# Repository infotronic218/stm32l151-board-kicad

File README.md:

# STM32L151 board design with KiCad 
The design files are available and free to use . The Bill of materials is in Excel format and be ordered from Mouser website. For Any project related question do not hesitate to message me thanks.
## Manufactured board view

## Board Layout 3D View 

## Board Layout View 2

## Board Layout View 2

# List of sensors used in the design 
* Accelorometer 
* Analog Temperature sensor
* Digital Humidity and temperature sensor (I2C)
* External Flash memory (16Mbits)
* Digital RGB LED (IN-PI554FCH)
* Simple LED

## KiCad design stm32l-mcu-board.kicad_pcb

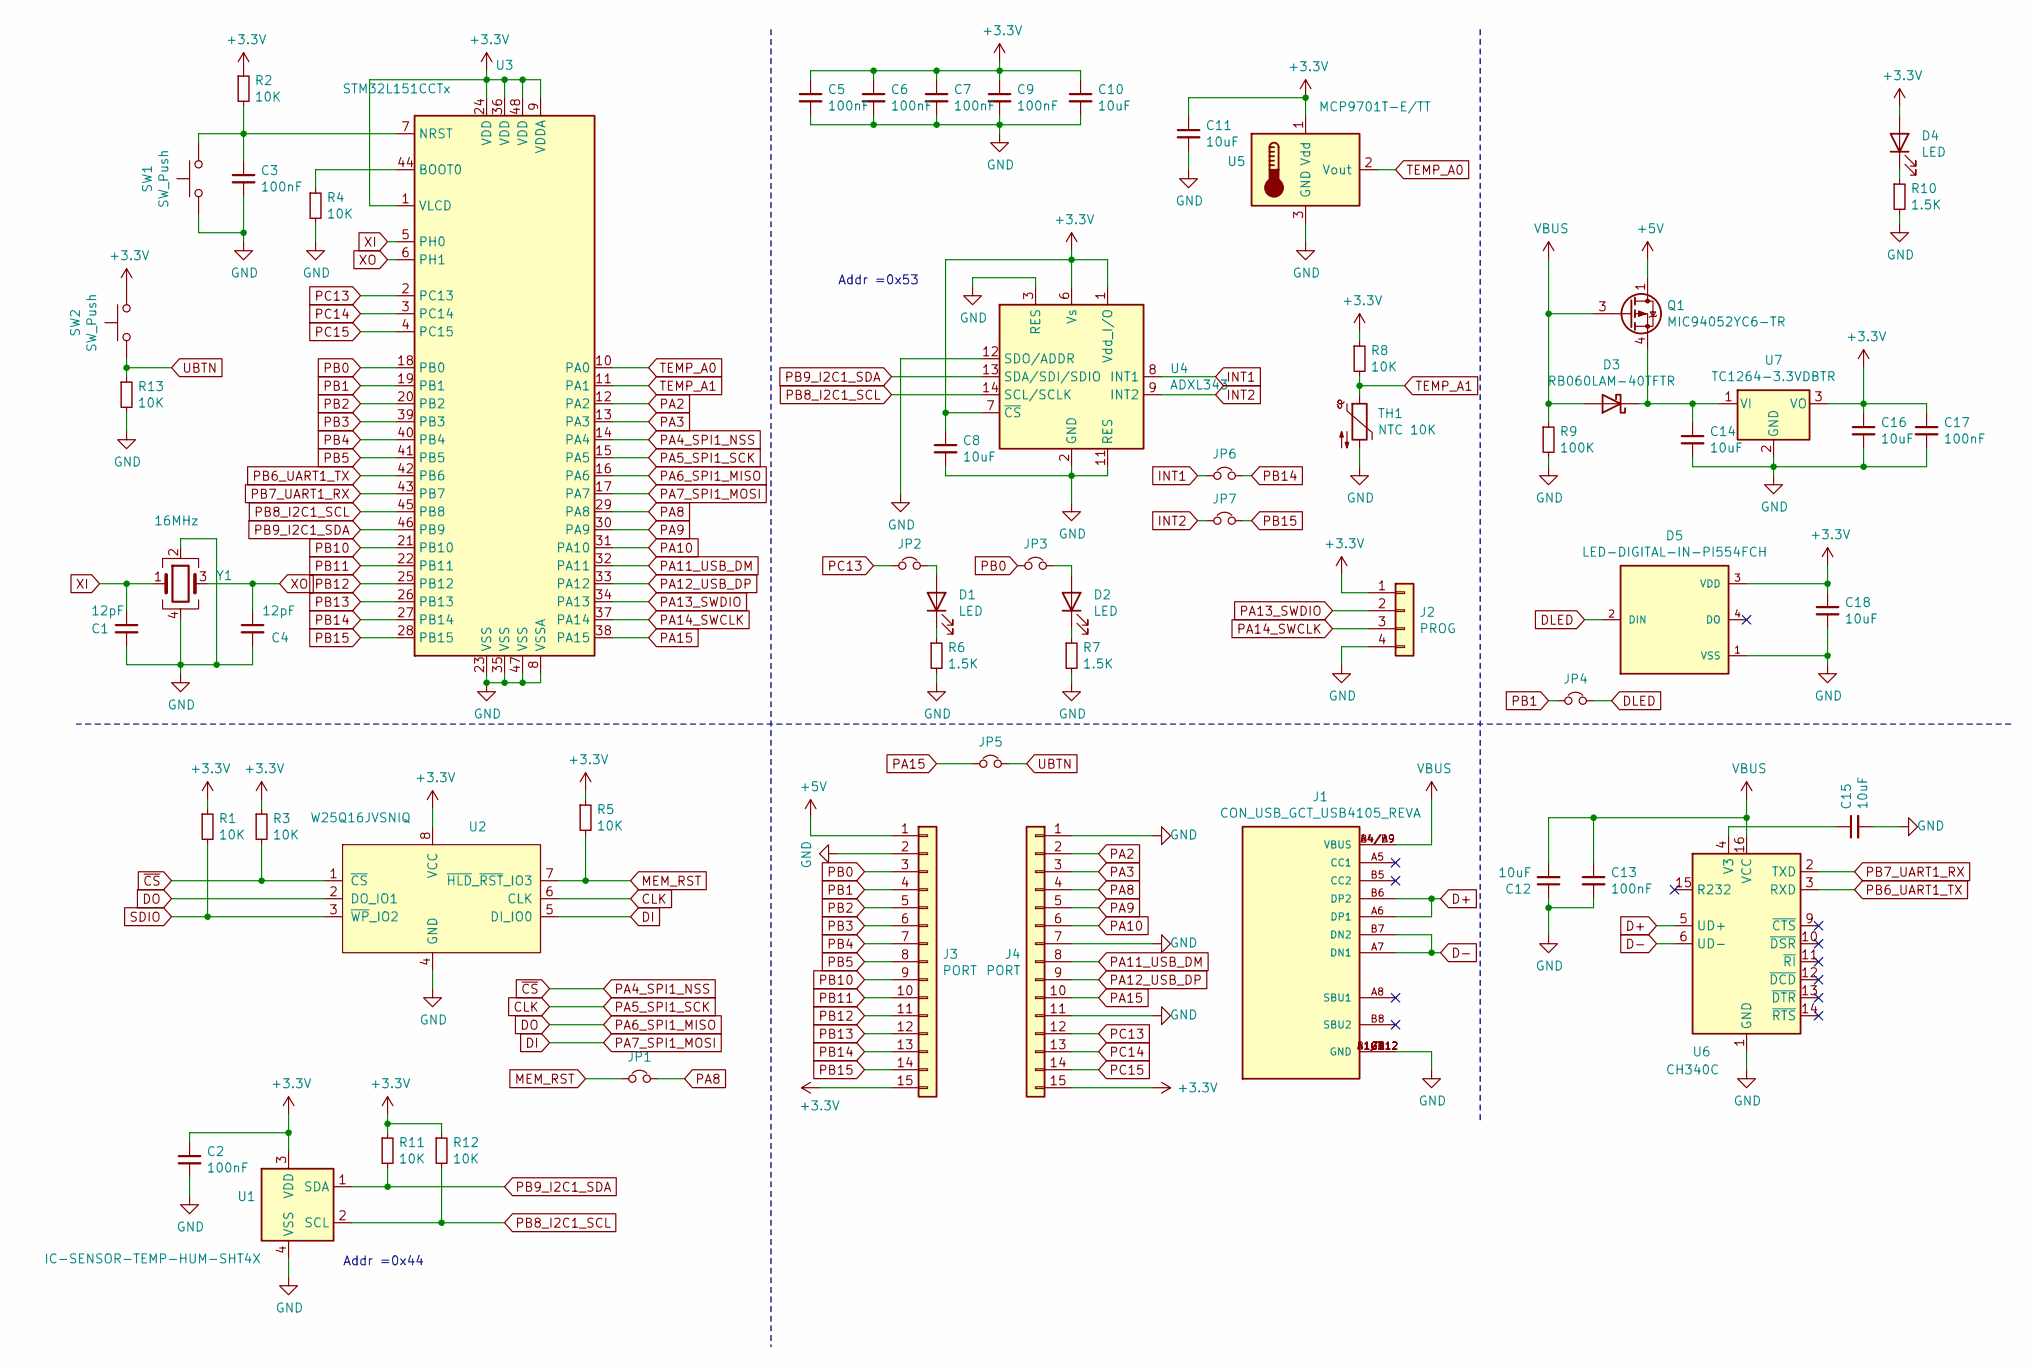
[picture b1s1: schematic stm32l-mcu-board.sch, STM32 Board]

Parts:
C1, C4: 12pF; C_0603_1608Metric; MPN 06035A120JAT2A; Mouser 581-06035A120J
C2, C3, C5, C6, C7, C9, C13, C17: 100nF; C_0603_1608Metric; MPN C0603C104K4RACTU; Mouser 80-C0603C104K4R
C8, C10, C11, C12, C14, C15, C16, C18: 10uF; C_0805_2012Metric; MPN C0805C106K3PACTU; Mouser 80-C0805C106K3P
D1, D2, D4: LED; LED_0805_2012Metric; MPN AP2012HD; Mouser 604-AP2012HD
D3: RB060LAM-40TFTR; D_SOD-128; MPN RB060LAM-40TFTR; Mouser 755-RB060LAM-40TFTR
D5: LED-DIGITAL-IN-PI554FCH; MPN IN-PI554FCH; Mouser 743-IN-PI554FCH
J1: CON_USB_GCT_USB4105_REVA; PARTREV 0.2; Mouser 640-USB4105-GF-A-060
J2: PROG; PinHeader_1x04_P2.54mm_Vertical
J3, J4: PORT; PinHeader_1x15_P2.54mm_Vertical
JP1, JP2, JP3, JP4, JP5, JP6, JP7: Jumper_NC_Small; SolderJumper-2_P1.3mm_Open_RoundedPad1.0x1.5mm
Q1: MIC94052YC6-TR; SOT-363_SC-70-6; MPN MIC94052YC6-TR; Mouser 998-MIC94052YC6TR
R1, R2, R3, R4, R5, R8, R11, R12, R13: 10K; R_0805_2012Metric; MPN CR0805-FX-1002ELF; Mouser 652-CR0805FX-1002ELF
R6, R7, R10: 1.5K; R_0805_2012Metric; MPN RCC08051K50FKEA; Mouser 71-RCC08051K50FKEA
R9: 100K; R_0805_2012Metric; MPN CHP0805AFX-1003ELF; Mouser 652-CHP0805AFX1003EL
SW1, SW2: SW_Push; SW_SPST_B3U-1000P-B
TH1: NTC 10K; R_0805_2012Metric; MPN ABNTC-0805-103J-3950F-T; Mouser 815-NTC805103J3950FT
U1: IC-SENSOR-TEMP-HUM-SHT4X; MPN SHT40-AD1B-R3; Mouser 403-SHT40-AD1B-R3
U2: W25Q16JVSNIQ; IC-FLASH-16MB-W25Q16JVSNIQ; MPN W25Q16JVSNIQ; Mouser 454-W25Q16JVSNIQ
U3: STM32L151CCTx; LQFP-48_7x7mm_P0.5mm; MPN STM32L151CCT6; Mouser 511-STM32L151CCT6
U4: ADXL343; LGA-14_3x5mm_P0.8mm_LayoutBorder1x6y; MPN ADXL343BCCZ-RL7; Mouser 584-ADXL343BCCZ-R7
U5: MCP9701T-E/TT; SOT-23; MPN MCP9701T-E/TT; Mouser 579-MCP9701T-E/TT
U6: CH340C; SOIC-16_3.9x9.9mm_P1.27mm
U7: TC1264-3.3VDBTR; SOT-223-3_TabPin2; MPN TC1264-3.3VDBTR; Mouser 579-TC1264-3.3VDBTR
Y1: 16MHz; Crystal_SMD_3225-4Pin_3.2x2.5mm; MPN CX3225SB16000E0EGFCC; Mouser 581-CX3225SB16000EGF

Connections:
+3V3: C2.1, C5.1, C6.1, C7.1, C8.1, C9.1, C10.1, C11.1, C16.1, C17.1, C18.1, D4.2 (A), D5.3 (VDD), J2.1, J3.15, J4.15, R1.1, R2.1, R3.1, R5.1, R8.1, R11.1, R12.1, SW2.2, U1.3 (VDD), U2.8 (VCC), U3.1 (VLCD), U3.9 (VDDA), U3.24 (VDD), U3.36 (VDD), U3.48 (VDD), U4.1 (Vdd_I/O), U4.6 (Vs), U4.7 (~CS), U5.1 (Vdd), U7.3 (VO)
+5V: J3.1, Q1.1 (D), Q1.2 (S), Q1.5 (D), Q1.6 (D)
CLK: U2.6 (CLK), U3.15 (PA5)
D+: J1.A6 (DP1), J1.B6 (DP2), U6.5 (UD+)
D-: J1.A7 (DN1), J1.B7 (DN2), U6.6 (UD-)
DI: U2.5 (DI_IO0), U3.17 (PA7)
DLED: D5.2 (DIN), JP4.2
DO: U2.2 (DO_IO1), U3.16 (PA6)
GND: C1.2, C2.2, C3.2, C4.2, C5.2, C6.2, C7.2, C8.2, C9.2, C10.2, C11.2, C12.1, C13.2, C14.2, C15.2, C16.2, C17.2, C18.2, D5.1 (VSS), J1.A1/B12 (GND), J1.B1/A12 (GND), J1.G1 (GND), J1.G2 (GND), J1.G3 (GND), J1.G4 (GND), J2.4, J3.2, J4.1, J4.7, J4.11, R4.2, R6.2, R7.2, R9.2, R10.2, R13.2, SW1.1, TH1.2, U1.4 (VSS), U2.4 (GND), U3.8 (VSSA), U3.23 (VSS), U3.35 (VSS), U3.47 (VSS), U4.2 (GND), U4.3 (RES), U4.4 (GND), U4.5 (GND), U4.11 (RES), U4.12 (SDO/ADDR), U5.3 (GND), U6.1 (GND), U7.2 (GND), Y1.2, Y1.4
INT1: JP6.1, U4.8 (INT1)
INT2: JP7.1, U4.9 (INT2)
MEM_RST: JP1.1, R5.2, U2.7 (~HLD~_~RST~_IO3)
unnamed: C3.1, R2.2, SW1.2, U3.7 (NRST)
unnamed: C14.1, D3.1 (K), Q1.4 (S), U7.1 (VI)
unnamed: C15.1, U6.4 (V3)
unnamed: D1.1 (K), R6.1
unnamed: D1.2 (A), JP2.2
unnamed: D2.1 (K), R7.1
unnamed: D2.2 (A), JP3.2
unnamed: D4.1 (K), R10.1
unnamed: R4.1, U3.44 (BOOT0)
PA2: J4.2, U3.12 (PA2)
PA3: J4.3, U3.13 (PA3)
PA4_SPI1_NSS: R3.2, U2.1 (~CS), U3.14 (PA4)
PA8: J4.4, JP1.2, U3.29 (PA8)
PA9: J4.5, U3.30 (PA9)
PA10: J4.6, U3.31 (PA10)
PA11_USB_DM: J4.8, U3.32 (PA11)
PA12_USB_DP: J4.9, U3.33 (PA12)
PA13_SWDIO: J2.2, U3.34 (PA13)
PA14_SWCLK: J2.3, U3.37 (PA14)
PA15: J4.10, JP5.1, U3.38 (PA15)
PB0: J3.3, JP3.1, U3.18 (PB0)
PB1: J3.4, JP4.1, U3.19 (PB1)
PB2: J3.5, U3.20 (PB2)
PB3: J3.6, U3.39 (PB3)
PB4: J3.7, U3.40 (PB4)
PB5: J3.8, U3.41 (PB5)
PB6_UART1_TX: U3.42 (PB6), U6.3 (RXD)
PB7_UART1_RX: U3.43 (PB7), U6.2 (TXD)
PB8_I2C1_SCL: R12.2, U1.2 (SCL), U3.45 (PB8), U4.14 (SCL/SCLK)
PB9_I2C1_SDA: R11.2, U1.1 (SDA), U3.46 (PB9), U4.13 (SDA/SDI/SDIO)
PB10: J3.9, U3.21 (PB10)
PB11: J3.10, U3.22 (PB11)
PB12: J3.11, U3.25 (PB12)
PB13: J3.12, U3.26 (PB13)
PB14: J3.13, JP6.2, U3.27 (PB14)
PB15: J3.14, JP7.2, U3.28 (PB15)
PC13: J4.12, JP2.1, U3.2 (PC13)
PC14: J4.13, U3.3 (PC14)
PC15: J4.14, U3.4 (PC15)
SDIO: R1.2, U2.3 (~WP~_IO2)
TEMP_A0: U3.10 (PA0), U5.2 (Vout)
TEMP_A1: R8.2, TH1.1, U3.11 (PA1)
UBTN: JP5.2, R13.1, SW2.1
VBUS: C12.2, C13.1, D3.2 (A), J1.A4/B9 (VBUS), J1.B4/A9 (VBUS), Q1.3 (G), R9.1, U6.16 (VCC)
XI: C1.1, U3.5 (PH0), Y1.1
XO: C4.1, U3.6 (PH1), Y1.3

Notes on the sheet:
Addr =0x44
Addr =0x53

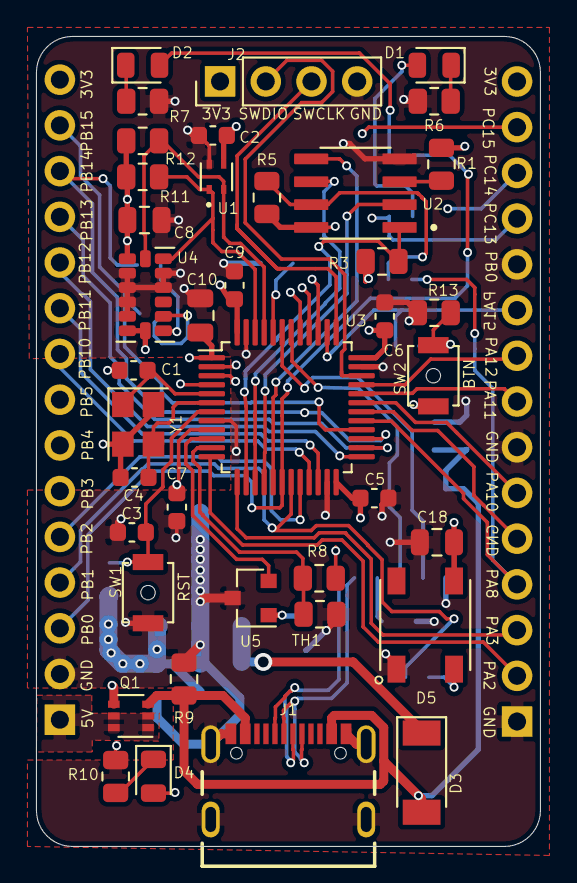
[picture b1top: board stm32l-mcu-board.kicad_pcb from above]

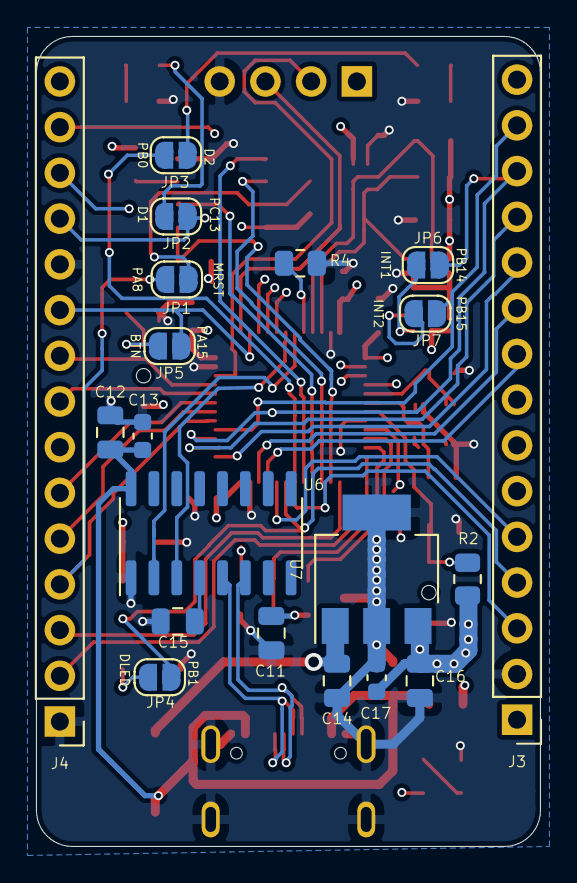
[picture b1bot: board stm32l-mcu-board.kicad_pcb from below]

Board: 4 copper layers, 28.0 x 45.0 mm, 59 parts (20 on the bottom side), 58 nets.

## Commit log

2022-01-21 Uploding the project to git
2022-01-21 Update the description
2022-08-03 Update the Flash memory circuit
